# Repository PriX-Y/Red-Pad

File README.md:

in case

case inside

case outside

case backplate

pcb footprint

pcb 3d model

schematic

BOM

40% of time is spent
20% of time is spent looking for footprints
30% learning how to do something
10% asking questions on Slac

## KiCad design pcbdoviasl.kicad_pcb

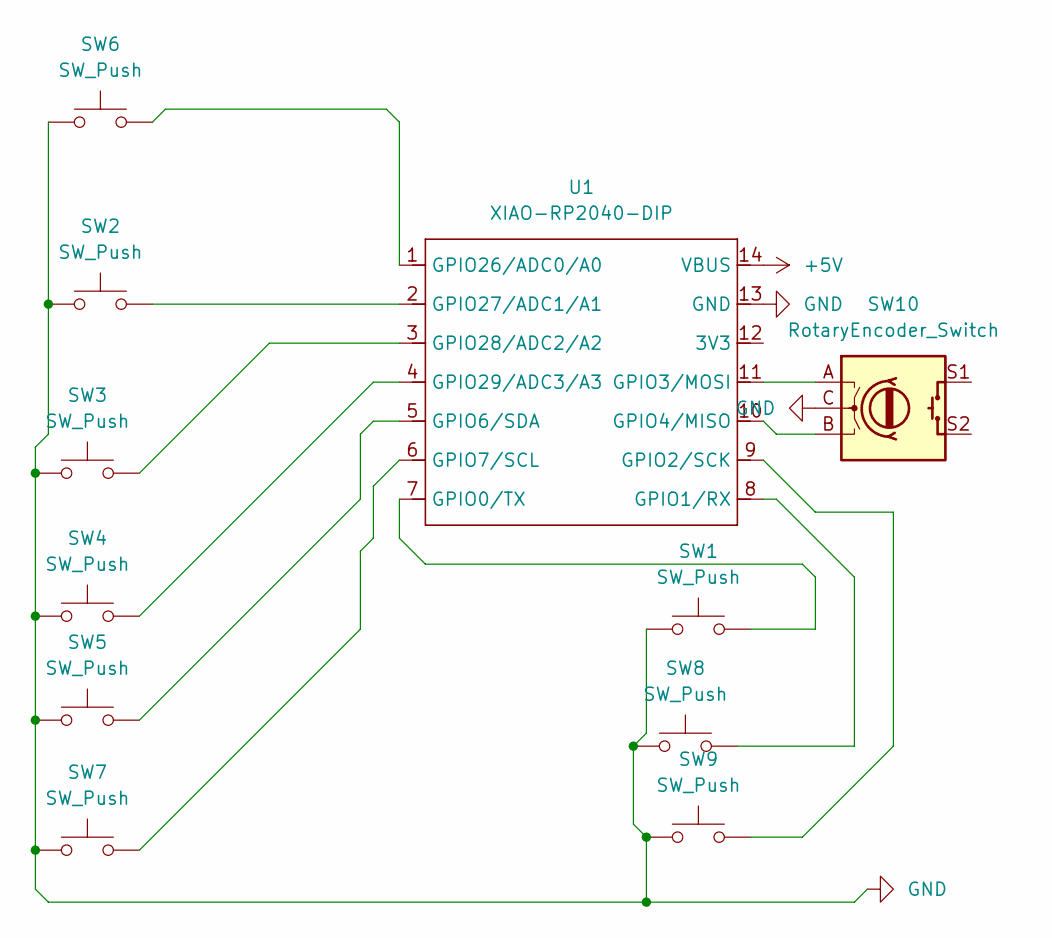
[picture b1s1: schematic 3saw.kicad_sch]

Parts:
SW1, SW2, SW3, SW4, SW5, SW6, SW7, SW8, SW9: SW_Push; MX-Hotswap-1U
SW10: RotaryEncoder_Switch; RotaryEncoder_Alps_EC11E-Switch_Vertical_H20mm_CircularMoun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
U1: XIAO-RP2040-DIP; XIAO-Generic-Hybrid-14P-2.54-21X17.8MM

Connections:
+5V: U1.14 (VBUS)
GND: SW1.1, SW2.1, SW3.1, SW4.1, SW5.1, SW6.1, SW7.1, SW8.1, SW9.1, SW10.C, U1.13 (GND)
unnamed: SW1.2, U1.7 (GPIO0/TX)
unnamed: SW8.2, U1.8 (GPIO1/RX)
unnamed: SW9.2, U1.9 (GPIO2/SCK)
unnamed: SW10.A, U1.11 (GPIO3/MOSI)
unnamed: SW10.B, U1.10 (GPIO4/MISO)
unnamed: SW5.2, U1.5 (GPIO6/SDA)
unnamed: SW7.2, U1.6 (GPIO7/SCL)
unnamed: SW6.2, U1.1 (GPIO26/ADC0/A0)
unnamed: SW2.2, U1.2 (GPIO27/ADC1/A1)
unnamed: SW3.2, U1.3 (GPIO28/ADC2/A2)
unnamed: SW4.2, U1.4 (GPIO29/ADC3/A3)

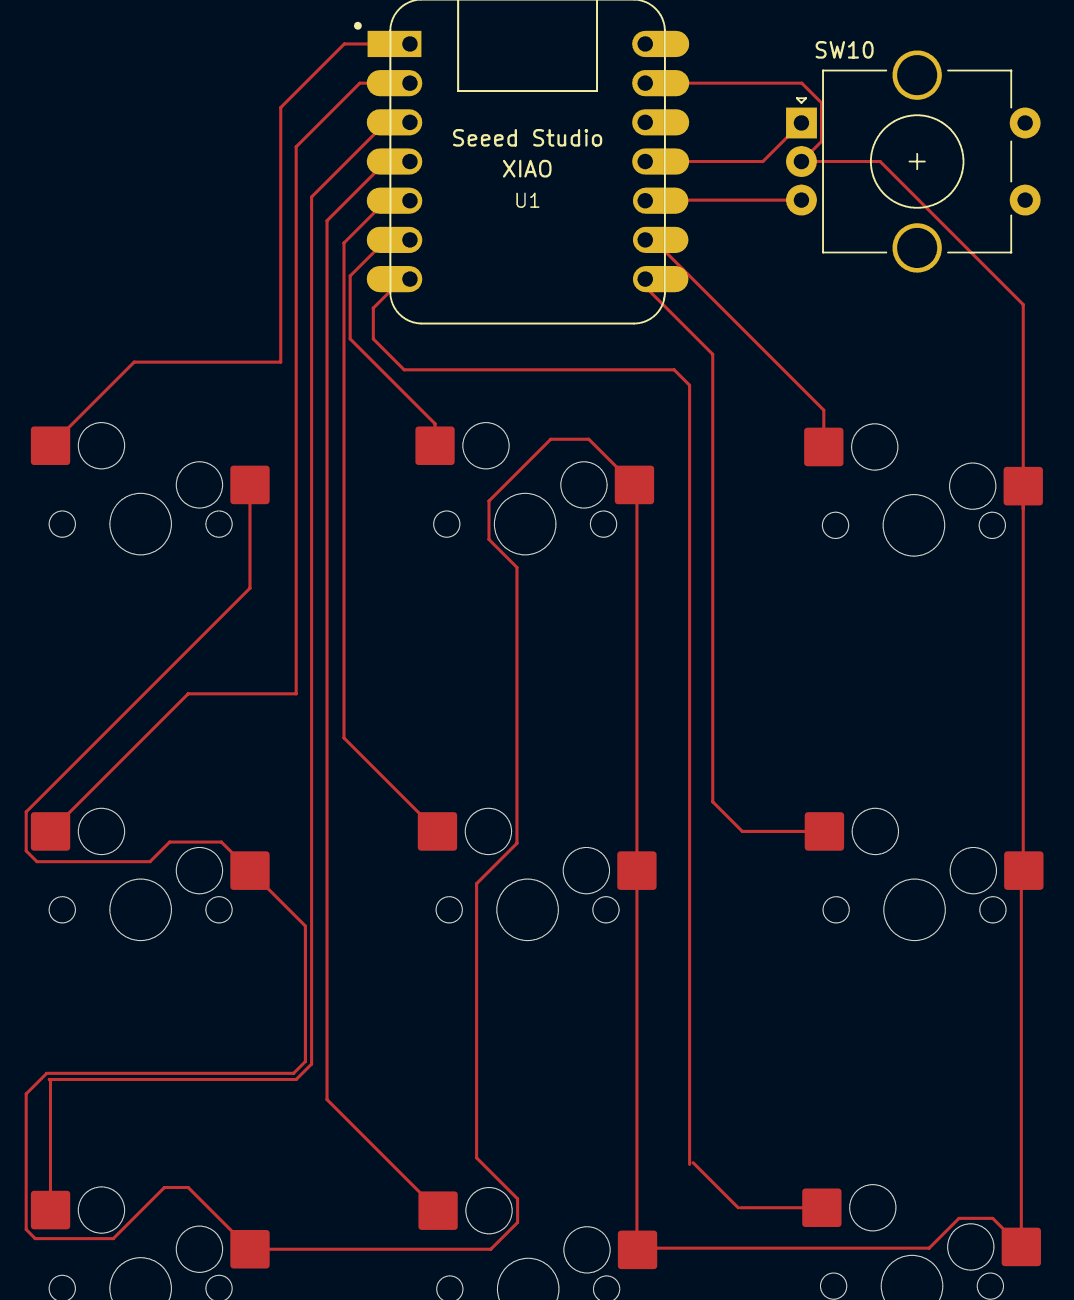
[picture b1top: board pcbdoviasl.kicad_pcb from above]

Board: 2 copper layers, 11 parts (0 on the bottom side), 12 nets.

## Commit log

2025-12-22 Update README with time spent statistics
    Add statistics on time spent in various activities.
2025-12-22 Create Code
2025-12-23 Add PCB footprint and 3D model sections to README
2025-12-23 Update all what i use
2025-12-23 Create Frameware code
